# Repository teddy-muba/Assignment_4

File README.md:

# uHat PCB design - Status LEDs submodule

In a large library building configuration where cubicles are used as small isolated study or reading spaces, it is a common thing to see readers, immediately after walking in, seeking for an available cubicle to occupy.
Similarly, in a vast office building scenario where the majority of the company operates on the floor, it is common practice for both workers and managers to book rooms for meetings during working hours. On the other hand, it is sometimes a ritual for individual employees to leave their floor desks to make use of meeting rooms to focus in solitude. Most times, this second case doesn’t require any formal booking of the meeting room.
Another instance or scenario we can think of is an indicating system at a banking facility or any other higher security building where only one person is admissible at a time.
 
Looking at the practicality of how things should operate in the above three scenarios, we should always expect situations where it won’t be time-effective for a new person entering the library to simply walk up towards the cubicles section to see if there is any unavailable place and return to the waiting area section if that is the case, only to make the same trip moments later to see if there is any available cubical - repeating the back-and-forth until so. The same thing can be thought of disturbances that can happen in meeting rooms scenarios where one can open the room to check its availability while there is a meeting happening in there at the same time.  
Lastly, what about the nightmare people will be experiencing at the entrance of a building requiring only one person to enter the facility at a time in case there is no proper indication system. 
 
We can solve these situations by using lights. Our idea is to make use of a Pi HAT designed with a bunch of LEDs to serve as occupancy indicators with the idea of using universal signs for green and red, where green means available and red means occupied. In this specific project, we will design and simulate a piHAT that will use 10 LEDs connected to the GPIO pins to simulate the occupancy indications for 10 cubicles, 10 meeting rooms or 10 entrances of banking facilities.

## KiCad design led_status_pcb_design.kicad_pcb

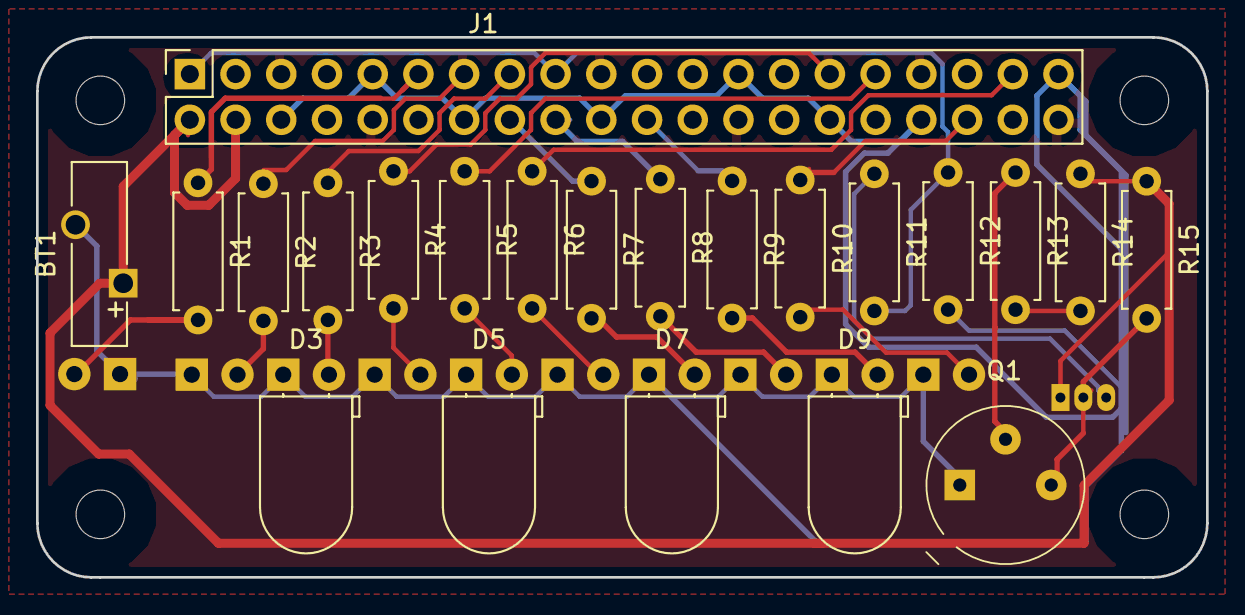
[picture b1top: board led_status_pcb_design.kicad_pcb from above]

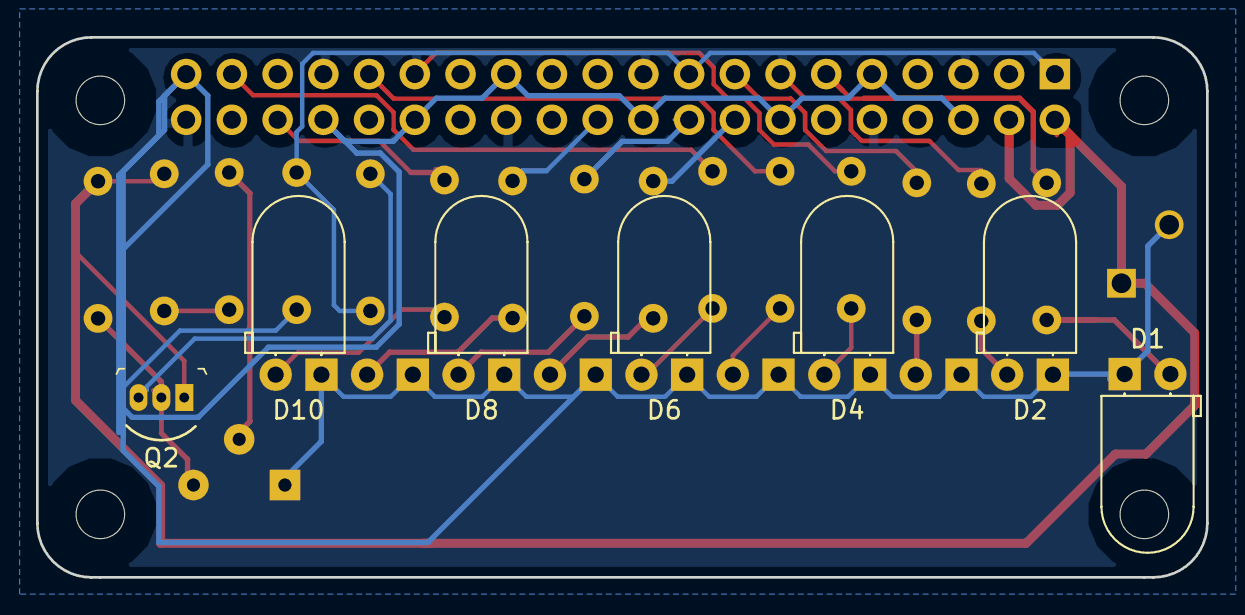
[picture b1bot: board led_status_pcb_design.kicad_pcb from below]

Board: 2 copper layers, 65.0 x 30.0 mm, 33 parts (7 on the bottom side), 27 nets.

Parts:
BT1: 5V supply; Battery_Panasonic_CR1025-VSK_Vertical_CircularHoles
D1, D2, D3, D4, D5, D6, D7, D8, D9, D10: CQY99; LED_D5.0mm_Horizontal_O1.27mm_Z3.0mm_IRGrey
H1, H2, H3, H4: MountingHole; MountingHole_2.7mm_M2.5_uHAT_RPi
J1: GPIO_CONNECTOR; PinSocket_2x20_P2.54mm_Vertical_Centered_Anchor
Q1: 2N2219; TO-39-3
Q2: 2N3905; TO-92-3
R1, R2, R3, R4, R5, R6, R7, R8, R9, R10: 300; R_Axial_DIN0207_L6.3mm_D2.5mm_P7.62mm_Horizontal
R11: 55; R_Axial_DIN0207_L6.3mm_D2.5mm_P7.62mm_Horizontal
R12: 10; R_Axial_DIN0207_L6.3mm_D2.5mm_P7.62mm_Horizontal
R13: 1k; R_Axial_DIN0207_L6.3mm_D2.5mm_P7.62mm_Horizontal
R14: 22k; R_Axial_DIN0207_L6.3mm_D2.5mm_P7.62mm_Horizontal
R15: 10k; R_Axial_DIN0207_L6.3mm_D2.5mm_P7.62mm_Horizontal

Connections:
+3V3: J1.1, J1.17, R11.2, R12.1
+5V: BT1.1, J1.2, J1.4, Q2.1, R14.1, R15.1
/GPIO5: J1.29, R4.1
/GPIO6: J1.31, R5.1
/GPIO16: J1.36, R10.1
/GPIO17_GEN0: J1.11, R1.1
/GPIO22_GEN3: J1.15, R3.1
/GPIO23_GEN4: J1.16, R7.1
/GPIO24_GEN5: J1.18, R8.1
/GPIO25_GEN6: J1.22, R9.1
/GPIO26: J1.37, R6.1
/GPIO27_GEN2: J1.13, R2.1
GND: BT1.2, D1.1, D2.1, D3.1, D4.1, D5.1, D6.1, D7.1, D8.1, D9.1, D10.1, J1.6, J1.9, J1.14, J1.20, J1.25, J1.30, J1.34, J1.39, Q1.1, R12.2
unnamed: D1.2, R1.2
unnamed: D2.2, R2.2
unnamed: D3.2, R3.2
unnamed: D4.2, R4.2
unnamed: D5.2, R5.2
unnamed: D6.2, R6.2
unnamed: D7.2, R7.2
unnamed: D8.2, R8.2
unnamed: D9.2, R9.2
unnamed: D10.2, R10.2
unnamed: Q1.2, R13.1
unnamed: Q1.3, Q2.2, R15.2
unnamed: Q2.3, R11.1
unnamed: R13.2, R14.2

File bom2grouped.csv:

Reference, Quantity, Value, Footprint, Datasheet
BT1 ,1,"5V supply","Battery:Battery_Panasonic_CR1025-VSK_Vertical_CircularHoles","~"
D1 D2 D3 D4 D5 D6 D7 D8 D9 D10 ,10,"CQY99","LED_THT:LED_D5.0mm_Horizontal_O1.27mm_Z3.0mm_IRGrey","https://www.prtice.info/IMG/pdf/CQY99.pdf"
H1 H2 H3 H4 ,4,"MountingHole","lib:MountingHole_2.7mm_M2.5_uHAT_RPi","~"
J1 ,1,"GPIO_CONNECTOR","lib:PinSocket_2x20_P2.54mm_Vertical_Centered_Anchor","~"
Q1 ,1,"2N2219","digikey-footprints:TO-39-3","http://www.onsemi.com/pub_link/Collateral/2N2219-D.PDF"
Q2 ,1,"2N3905","digikey-footprints:TO-92-3","https://www.nteinc.com/specs/original/2N3905_06.pdf"
R1 R2 R3 R4 R5 R6 R7 R8 R9 R10 ,10,"300","Resistor_THT:R_Axial_DIN0207_L6.3mm_D2.5mm_P7.62mm_Horizontal","~"
R11 ,1,"55","Resistor_THT:R_Axial_DIN0207_L6.3mm_D2.5mm_P7.62mm_Horizontal","~"
R12 ,1,"10","Resistor_THT:R_Axial_DIN0207_L6.3mm_D2.5mm_P7.62mm_Horizontal","~"
R13 ,1,"1k","Resistor_THT:R_Axial_DIN0207_L6.3mm_D2.5mm_P7.62mm_Horizontal","~"
R14 ,1,"22k","Resistor_THT:R_Axial_DIN0207_L6.3mm_D2.5mm_P7.62mm_Horizontal","~"
R15 ,1,"10k","Resistor_THT:R_Axial_DIN0207_L6.3mm_D2.5mm_P7.62mm_Horizontal","~"
U1 ,1,"LTC4414","Package_SO:MSOP-8_3x3mm_P0.65mm","http://cds.linear.com/docs/en/datasheet/4414fc.pdf"

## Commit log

2021-06-14 libraries
2021-06-14 project definition
2021-06-14 project schematics
2021-06-14 project pcb
2021-06-14 gerbers files
2021-06-14 BOMs
2021-06-14 Specifications
2021-06-14 simulated circuit
2021-06-14 Outstanding bugs

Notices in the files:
led_status_pcb_design.kicad_pcb:
This PCB design is licensed under MIT Open Source License.
